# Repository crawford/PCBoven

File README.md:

PCBoven
=======

Reflow your toast.

'''Note''': Use this design at your own risk. I am not responsible for damaged
hardware or scorched apartments.

This is a USB host controlled DIY reflow oven. The aim of the project is to take
a cheap toaster oven and turn it into a temperature controlled reflow oven. The
oven itself is retrofitted with a custom control circuit which communicates over
USB with a host. The onboard oven controller is relatively simple, taking simple
commands (e.g. set target temperature) and reporting its state periodically. The
host application is the component that actually interpolates the reflow profile
and intructs the oven to hit target temperatures at certain times.

This implementation is broken into three components: firmware, device driver,
and control application, detailed below.

#Firmware#
The oven is controlled via the ATmega32u4 (in my case, the Adafruit ATmega32u4
breakout board), though another USB-enabled Atmel MCU could be specified in the
build process. The controller is designed to control two heating elements
independantly of one another in order to achieve a more even heating. Please,
refer to the [[schematic]] for details.

The firmware on the controller is communicates with the device driver using a
bulk endpoint (commands sent from the host to the device) and an interrupt
endpoint (periodic state (sent from the device to the host). Both endpoints
sent data using the same format (one for commands and one for state updates),
a packed structure of flags, for simplicity.

The firmware is responsible for properly controlling the temperature. The goal
is to quickly and accurately regulate the temperature with a fast response time
and low overshoot. Currently, there is no control algorithm and the performance
is less than ideal. Eventually, I'll implement a PD or PID controller (but no
autotuning (sorry T-Pain) so you'll have to provide your own values).

#Device Driver#
The device driver is written as a loadable kernel module for Linux (tested on
version 3.2 of the kernel). It registers itself as a miscellaneous device on
module load which creates the /dev/pcboven node (this node can only be used to
call ioctls). The driver also registers a USB device driver which gets loaded
when the oven controlled is connected to the host. The USB device driver
exposes a series of sysfs entries (e.g. probe temperature, fault flags, target
oven temperature) which can be used for debugging.

Control and monitoring of the oven is achieved through ioctl calls to the
/dev/pcboven node. This node is capable of sending SIGIO signals to the current
file owner. The signals are sent whenever a new state is received from the oven
or when the oven has been connected/disconnected. This mechanism is used
heavily by the control application and allows it to asynchronously monitor
connectivity and state.

#Control Application#
The control application is a relatively simple GUI front-end to this system.
It takes one command-line parameter, the path to the reflow profile. The profile
consists of a series of timestamps and temperatures which describe the intended
temperature/time curve (an example profile is included in the application
directory). The application interpolates the profile into a series of
temperature targets at one second intervals. This is what allows the oven to
smoothly follow the reflow curve.

The control application allows the user to monitor and control the reflow
sequence. At any point, the user can stop or start the sequence and view system
statistics. A temperature/time graph for both the target and actual oven
temperature is created in realtime. This allows the user to calibrate the oven
before use and to ensure that the sequence reached adequate temperatures during
use.

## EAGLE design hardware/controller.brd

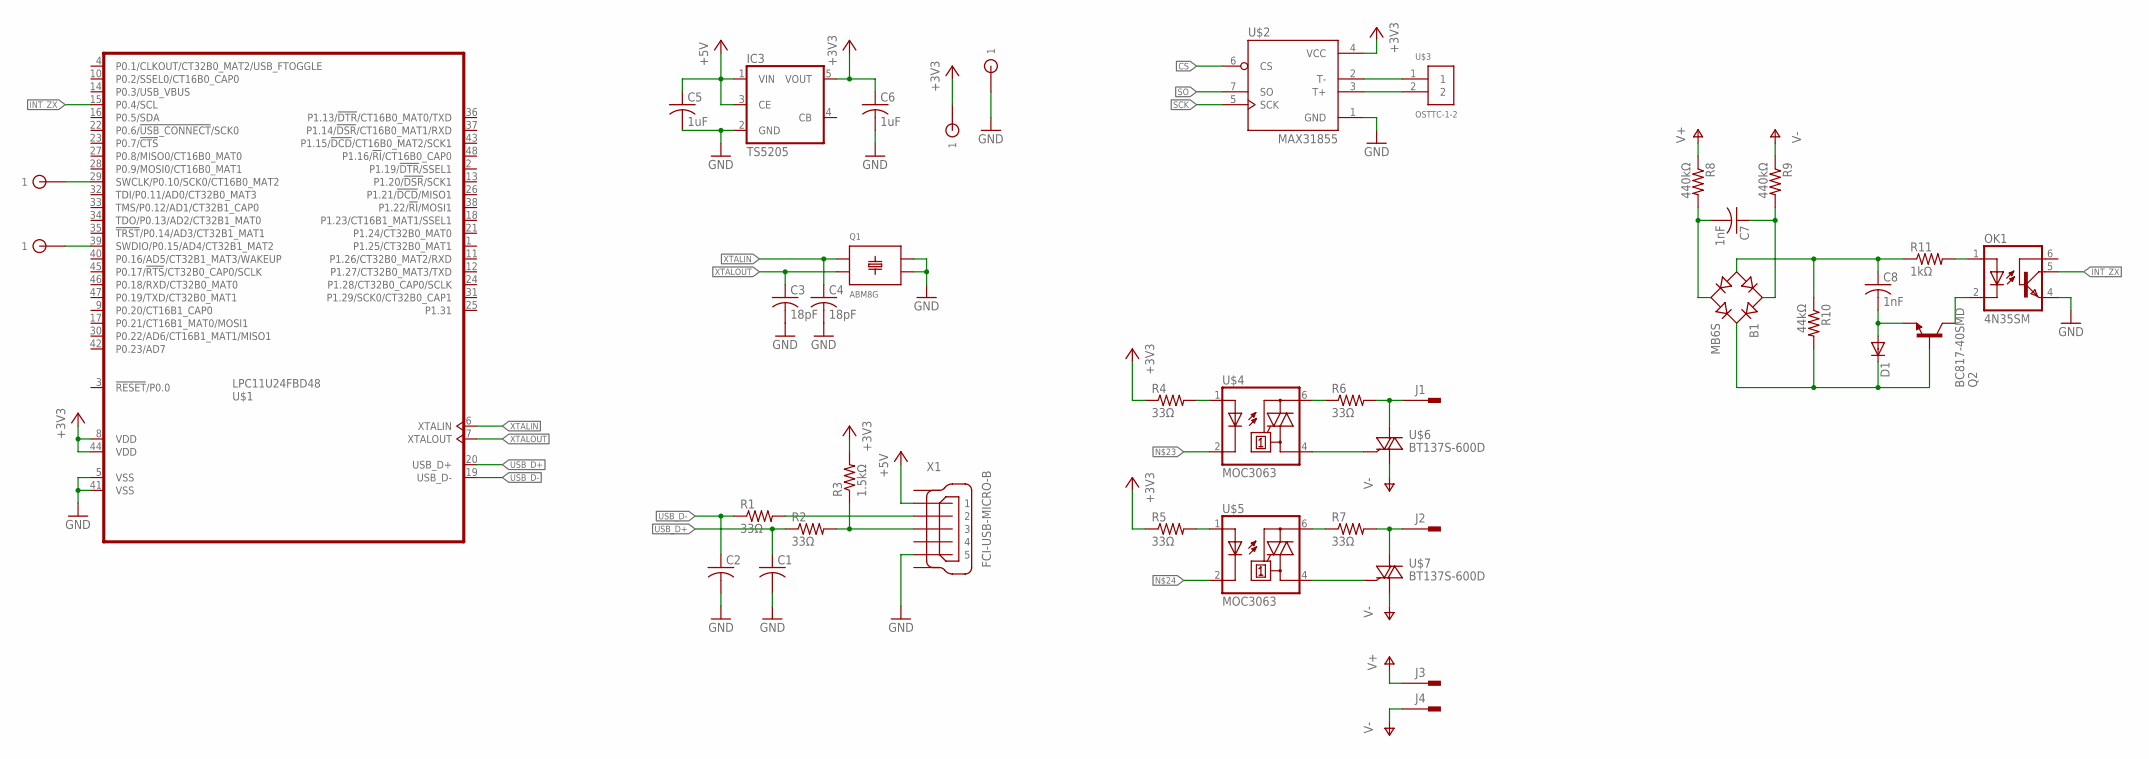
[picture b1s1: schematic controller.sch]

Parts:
B1: MB6S; SOIC-4
C1, C2: C-USC0402; C0402
C3, C4: 18pF; C0402K
C5, C6: 1uF; C0402K
C7, C8: 1nF; C0402K
D1: DIODE-SOD80C; SOD80C
IC3: TS5205; SOT25
J1, J2, J3, J4: PIN2F061.100; F061.100
OK1: 4N35SM; DIL6-SMD
Q1: ABM8G; SMD-4
Q2: BC817-40SMD; SOT23-BEC
R1, R2, R4, R5, R6, R7: 33Ω; R0402
R3: 1.5kΩ; R0402
R8, R9: 440kΩ; R0402
R10: 44kΩ; R0402
R11: 1kΩ; R0402
TP1, TP2, TP6, TP7: TESTPOINT; TESTPOINT-SMD
U$1: LPC11U24FBD48; LQFP48
U$2: MAX31855; SO08
U$3: OSTTC-1-2
U$4, U$5: MOC3063; SMD6
U$6, U$7: BT137S-600D; TO-252
X1: FCI-USB-MICRO-B; FCI-MICRO-USB-B

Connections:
+3V3: C6.1, IC3.5 (VOUT), R3.2, R4.1, R5.1, TP6.1, U$1.8 (VDD), U$1.44 (VDD), U$2.4 (VCC)
+5V: C5.1, IC3.1 (VIN), IC3.3 (CE), X1.1
CS: U$2.6 (CS)
G1: X1.M1 (G1)
G2: X1.M2 (G2)
GND: C1.2, C2.2, C3.2, C4.2, C5.2, C6.2, IC3.2 (GND), OK1.4 (EMI), Q1.2 (GND1), Q1.4 (GND2), TP7.1, U$1.5 (VSS), U$1.41 (VSS), U$2.1 (GND), X1.5
INT_ZX: OK1.5 (COL), U$1.15 (P0.4/SCL)
unnamed: R6.1, U$4.6 (A2)
unnamed: J2.A1, J2.A2, R7.2, U$7.1 (A2)
unnamed: R1.2, X1.2
unnamed: U$2.2 (T-), U$3.1
unnamed: U$2.3 (T+), U$3.2
unnamed: TP2.1, U$1.29 (SWCLK/P0.10/SCK0/CT16B0_MAT2)
unnamed: R2.2, R3.1, X1.3
unnamed: R7.1, U$5.6 (A2)
unnamed: TP1.1, U$1.39 (SWDIO/P0.15/AD4/CT32B1_MAT2)
unnamed: R4.2, U$4.1 (A)
unnamed: R5.2, U$5.1 (A)
unnamed: J1.A1, J1.A2, R6.2, U$6.1 (A2)
unnamed: U$4.4 (A1), U$6.2 (G)
unnamed: U$5.4 (A1), U$7.2 (G)
unnamed: B1.-, C8.1, R10.1, R11.1
unnamed: B1.+, D1.C, Q2.B, R10.2
unnamed: B1.~1 (AC1), C7.1, R9.2
unnamed: B1.~2 (AC2), C7.2, R8.2
unnamed: OK1.1 (A), R11.2
unnamed: OK1.2 (C), Q2.C
unnamed: C8.2, D1.A, Q2.E
SCK: U$2.5 (SCK)
SO: U$2.7 (SO)
USB_D+: C1.1, R2.1, U$1.20 (USB_D+)
USB_D-: C2.1, R1.1, U$1.19 (USB_D-)
V+: J3.A1, J3.A2, R8.1
V-: J4.A1, J4.A2, R9.1, U$6.3 (A1), U$7.3 (A1)
XTALIN: C4.1, Q1.1, U$1.6 (XTALIN)
XTALOUT: C3.1, Q1.3 (2), U$1.7 (XTALOUT)

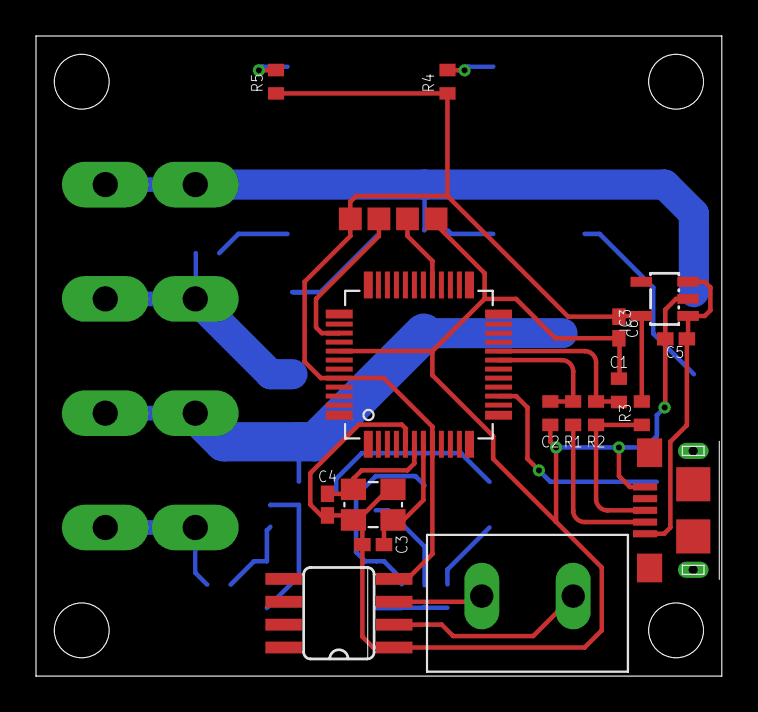
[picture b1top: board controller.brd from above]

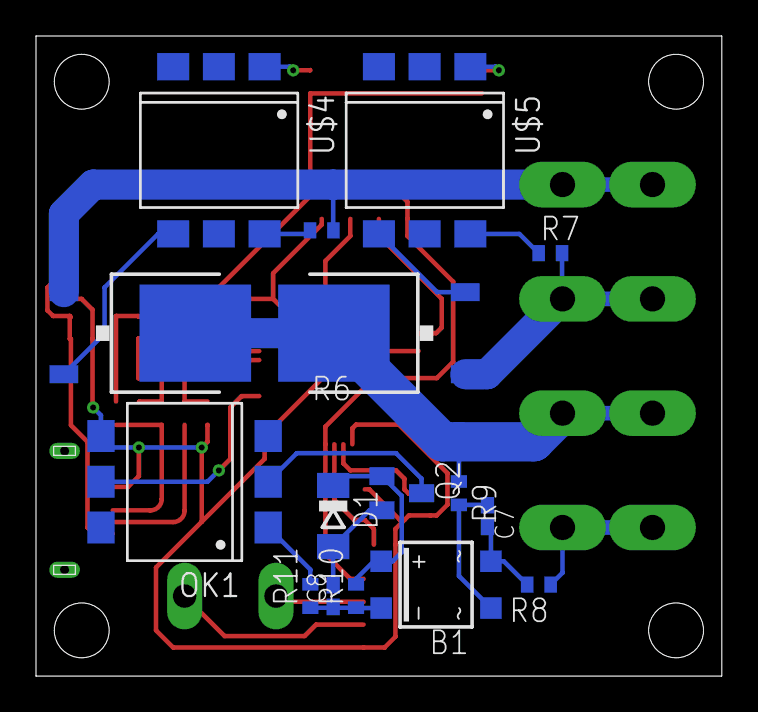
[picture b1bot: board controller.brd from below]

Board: 2 copper layers, 38.1 x 35.6 mm, 41 parts (16 on the bottom side), 31 nets.

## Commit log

2013-02-07 Changing read rate to 1Hz
2013-02-07 Adding initial filament code -Added a braindead temperature control implementation
2013-02-08 Adding MAX31855 and USB support -Haven't tested this (it compiles)
2013-02-09 Got USB comm working -Reverted LUFA back to a previous version (following up with Dean) -Set up poll timer
2013-02-13 Finishing MAX31855 driver -Verified in the freezer and the oven
2013-02-14 Committing the USB driver
2013-02-14 Changing USB device product id
2013-02-15 Adding driver support for filaments -Fixed bug in filament code
2013-02-15 Adding target temp to driver -Adding filament enable to firmware
2013-02-16 Changing pin definitions -Changed pins to the board pinout -Upped USB current to support two relays (200mA each)
2013-02-17 Finalizing prototype -Fixed sys entries -Fixed pinout -Fixed error handling
2013-02-17 Initial commit for control app
2013-02-18 Fixing spacing
2013-02-19 Adding oven manager -Created IoctlWorker and UdevMonitor
2013-02-20 Adding ReflowGraphWidget
2013-02-22 Adding ioctls
2013-02-22 Adding ioctl support to application and driver
2013-02-23 Fixing driver -Transmit whenever temperature or filaments are changed
2013-02-23 Added reflow profiles and parser
2013-02-23 Using args
2013-02-26 Using miscdevice in addition to usbdevice -Updated ioctls -Removed udev_monitor -Set up signal handling
2013-02-27 SIGIO works
2013-02-27 Added target following
2013-02-27 Reflow sequence works properly now -Fixed temperatures
2013-03-01 Added dummy device
2013-03-01 Fixing probe/remove behavior for application
2013-03-02 Adding reflow profile interpolation
2013-03-05 Expanding README -Added description
2013-03-05 Fixing compilation bug
2013-08-25 Updating LUFA
2013-08-26 Adding control requests
2013-08-26 Adding libusb-1.0 -Can connect to device -No communication -No hotswap
2013-08-26 Removing OUT endpoint
2013-08-28 Adding irq handler
2013-08-28 Using libusb_le16_to_cpu instead of ntohs
2013-08-28 Application compiles on windows now
2013-08-28 Correcting temperatures -Cleaned up buffer
2013-08-29 Fixing the USB device descriptors
2013-08-29 Fixing USB request buffer size
2013-12-29 Fixing typo in sed statement in Makefile.
2014-12-13 hardware: initial attempt with relays
2014-12-14 hardware: first attempt with triacs
2015-09-30 Fixed typographical error, changed appartment to apartment in README.
2015-09-30 Fixed typographical error, changed appartments to apartments in README.
